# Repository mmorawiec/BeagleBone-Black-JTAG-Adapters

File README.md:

# BeagleBone Black JTAG Adapters
BeagleBone Black JTAG Adapters converting Compact TI (CTI) 20 pin header to other JTAG headers.

## BBB_JTAG_CTI20_SMT_ARM20_SMT
BeagleBone Black JTAG adapter converting Compact TI (CTI) 20 pin header to ARM 20 pin header.
Two sided PCB with vertical SMD CTI20 and IDC20 connectors.

## BBB_JTAG_CTI20_SMT_TI20_SMT
BeagleBone Black JTAG adapter converting Compact TI (CTI) 20 pin header to TI 20 pin header.
Two sided PCB with vertical SMD CTI20 and IDC20 connectors.

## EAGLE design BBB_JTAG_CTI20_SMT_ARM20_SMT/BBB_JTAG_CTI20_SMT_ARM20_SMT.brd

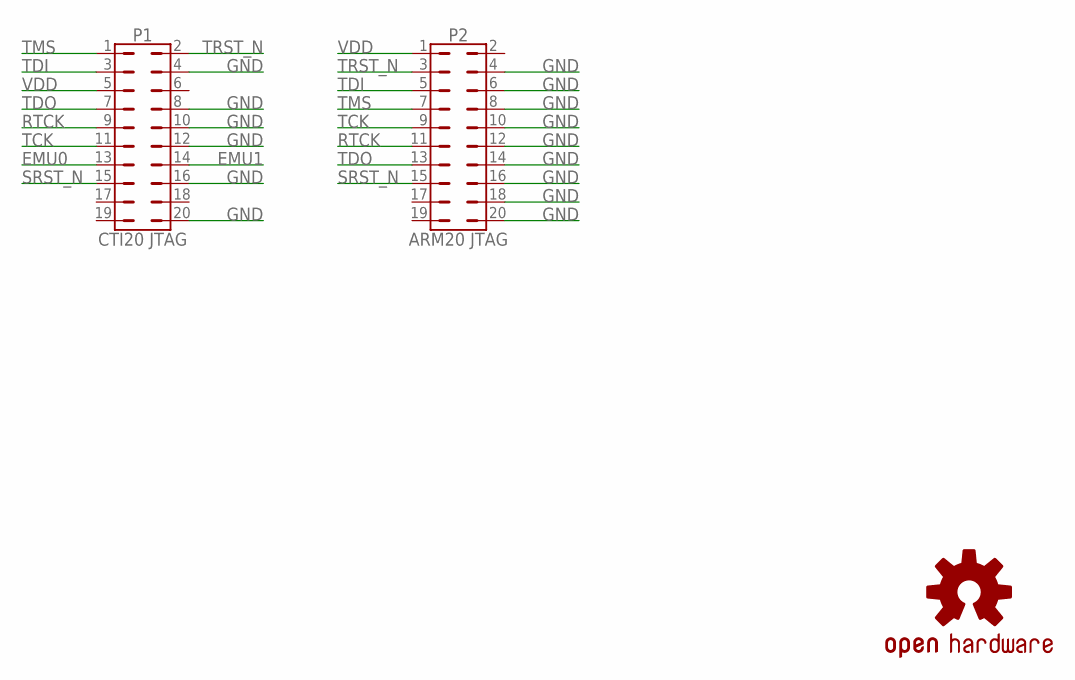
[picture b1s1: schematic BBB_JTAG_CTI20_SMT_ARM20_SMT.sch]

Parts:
LOGO1: OSHW-LOGOS; OSHW-LOGO-S
P1: CTI20 JTAG; M52-5151045
P2: ARM20 JTAG; T821M120A1S100CEU-B

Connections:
EMU0: P1.13
EMU1: P1.14
GND: P1.4, P1.8, P1.10, P1.12, P1.16, P1.20, P2.4, P2.6, P2.8, P2.10, P2.12, P2.14, P2.16, P2.18, P2.20
RTCK: P1.9, P2.11
SRST_N: P1.15, P2.15
TCK: P1.11, P2.9
TDI: P1.3, P2.5
TDO: P1.7, P2.13
TMS: P1.1, P2.7
TRST_N: P1.2, P2.3
VDD: P1.5, P2.1

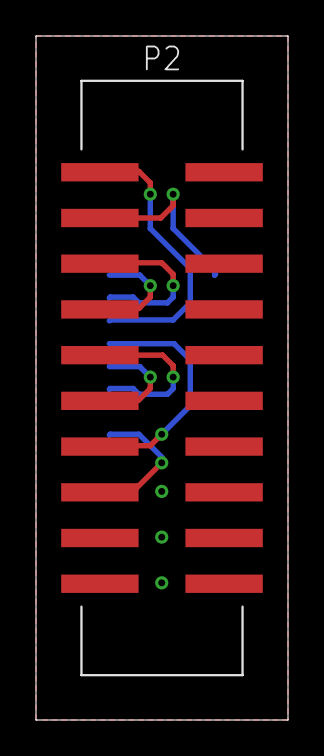
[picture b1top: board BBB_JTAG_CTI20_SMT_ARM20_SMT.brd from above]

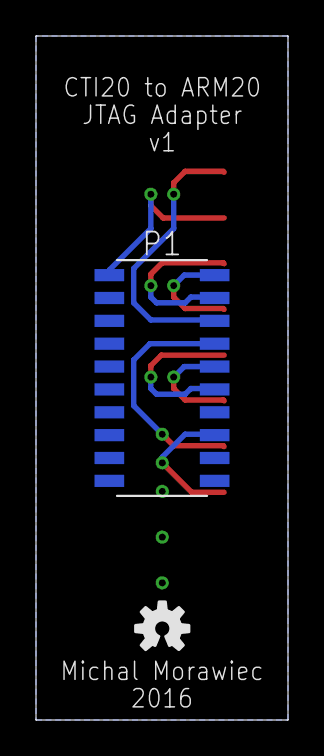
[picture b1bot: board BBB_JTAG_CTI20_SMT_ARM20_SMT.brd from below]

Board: 2 copper layers, 14.0 x 38.0 mm, 3 parts (2 on the bottom side), 9 nets.

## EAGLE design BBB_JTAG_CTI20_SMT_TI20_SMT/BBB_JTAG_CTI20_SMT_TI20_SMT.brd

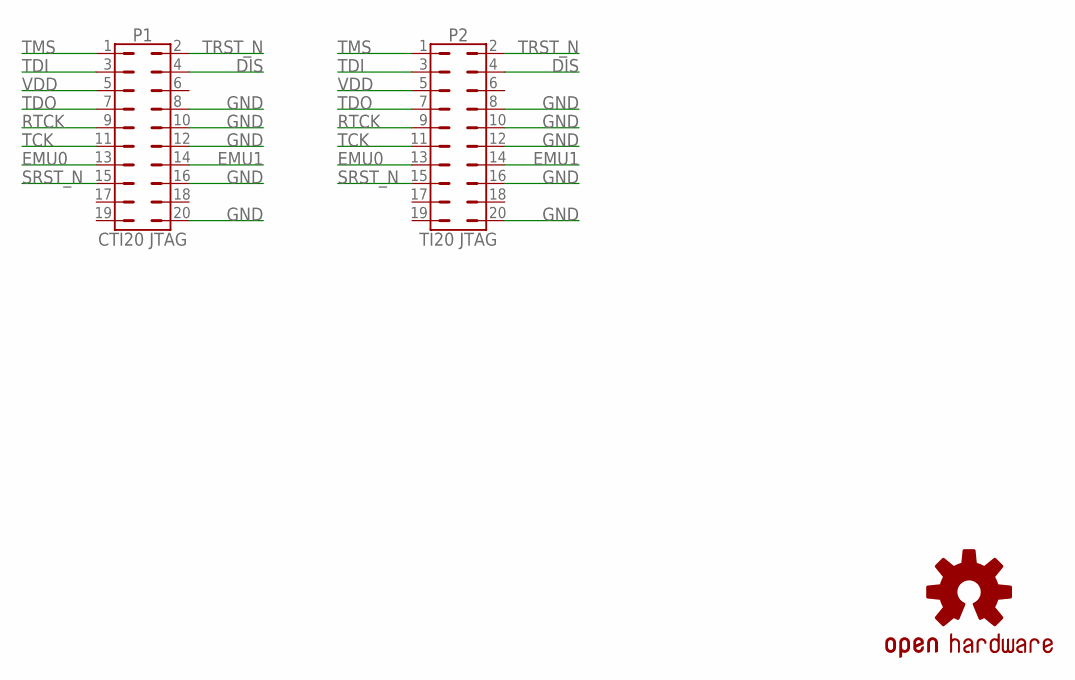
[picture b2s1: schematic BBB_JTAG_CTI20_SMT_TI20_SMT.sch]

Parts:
LOGO1: OSHW-LOGOS; OSHW-LOGO-S
P1: CTI20 JTAG; M52-5151045
P2: TI20 JTAG; T821M120A1S100CEU-B

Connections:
DIS: P1.4, P2.4
EMU0: P1.13, P2.13
EMU1: P1.14, P2.14
GND: P1.8, P1.10, P1.12, P1.16, P1.20, P2.8, P2.10, P2.12, P2.16, P2.20
RTCK: P1.9, P2.9
SRST_N: P1.15, P2.15
TCK: P1.11, P2.11
TDI: P1.3, P2.3
TDO: P1.7, P2.7
TMS: P1.1, P2.1
TRST_N: P1.2, P2.2
VDD: P1.5, P2.5

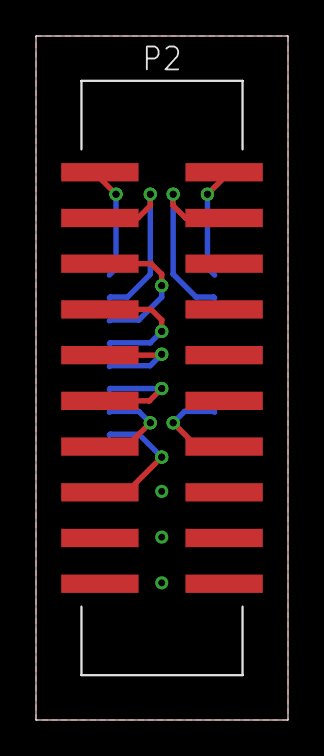
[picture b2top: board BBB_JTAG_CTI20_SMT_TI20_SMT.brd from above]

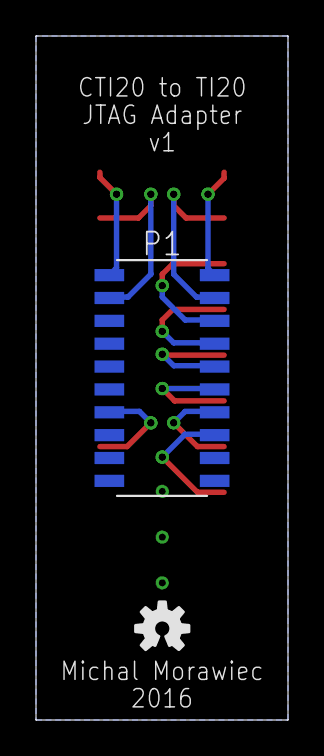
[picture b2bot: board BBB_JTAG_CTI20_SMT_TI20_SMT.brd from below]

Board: 2 copper layers, 14.0 x 38.0 mm, 3 parts (2 on the bottom side), 12 nets.

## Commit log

2016-06-12 Initial version
2016-06-28 Reroute to make P1 silkscreen fully visible
2023-09-27 Provide a kicad version
    Provide a converted version for ready consumption by Kicad users
    Generated with Kicad version 7.0.7

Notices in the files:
parts and their libraries:
SparkFun-Aesthetics: Licensing: Creative Commons ShareAlike 4.0 International - https://creativecommons.org/licenses/by-sa/4.0
